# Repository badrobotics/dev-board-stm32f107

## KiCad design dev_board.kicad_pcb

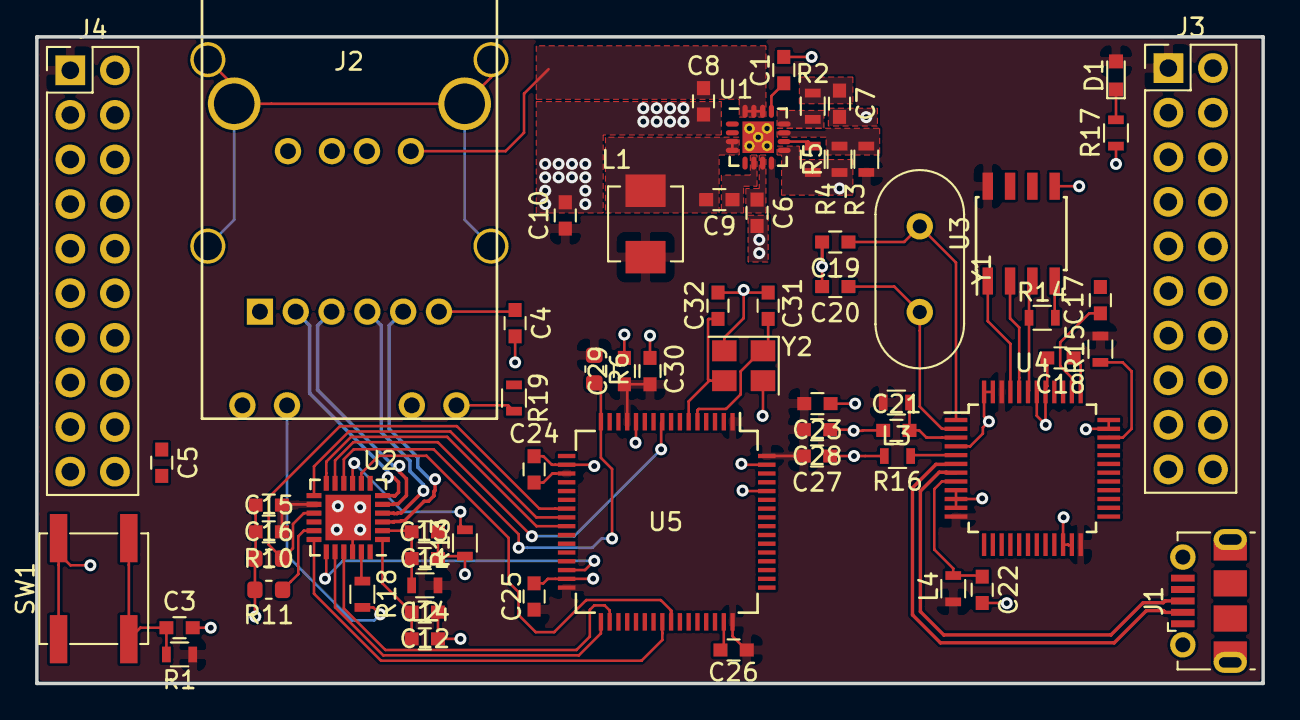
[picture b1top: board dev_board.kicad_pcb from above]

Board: 2 copper layers, 69.9 x 36.8 mm, 63 parts (0 on the bottom side), 59 nets.

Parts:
C1: 2200p; C_0603
C3, C17, C18, C19, C20, C21, C22, C31, C32: C_Small; C_0603
C4, C5: 0.1uF; C_0603
C6: 2.2u; C_0603
C7: 330p; C_0603
C8, C11, C12, C15: 22u; C_0603
C9, C13, C14, C16: 0.1u; C_0603
C10: 47u; C_0603
C23, C24, C25, C26, C27: 100nF; C_0603
C28: 4.7uF; C_0603
C29: 10nF; C_0603
C30: 1uF; C_0603
D1: LED; LED_0603
J1: USB_B_Micro; USB_Micro-B_Molex-105017-0001
J2: ARJ-169
J3, J4: Conn_02x10_Odd_Even; Pin_Header_Straight_2x10_Pitch2.54mm
L1: 0.47u; L_Vishay_IHLP-1616
L2: Ferrite_Bead; L_0603
L3, L4: Ferrite_Bead_Small; L_0603
R1: 10k; R_0603
R2: 20k; R_0603
R3: 210k; R_0603
R4: 115k; R_0603
R5: 25.5; R_0603
R6, R10: 1K; R_0603_1608Metric
R11: 10K; R_0603_1608Metric
R13: 6.49K 1%; R_0603
R14, R15, R16: R_Small; R_0603
R17, R18, R19: R; R_0603
SW1: SW_Push; SW_SPST_EVPBF
U1: LTC3604_UD; QFN-16-1EP_3x3mm_Pitch0.5mm_ThermalVias
U2: KSZ8081RND; QFN-24-1EP_4x4mm_Pitch0.5mm
U3: 93LCxxB; SOIC-8_3.9x4.9mm_Pitch1.27mm
U4: FT232H; LQFP-48_7x7mm_Pitch0.5mm
U5: STM32F107RCTx; LQFP-64_10x10mm_Pitch0.5mm
Y1: Crystal; Crystal_HC49-U_Vertical
Y2: Crystal_GND24; Crystal_SMD_3225-4pin_3.2x2.5mm

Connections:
+1V8: C17.1, U4.38
+3V3: C10.1, C15.1, C16.1, C23.2, C24.2, C25.2, C26.2, C27.2, C28.2, C29.1, C30.1, D1.2, J3.1, J4.1, L1.2, L2.2, L3.2, L4.2, R1.1, R4.1, R6.1, R15.2, U1.8, U2.14, U3.8, U4.12, U4.24, U4.39, U4.40, U4.46, U5.1, U5.13, U5.19, U5.32, U5.48, U5.64
+5V: C8.1, J2.U1, J3.2, J4.2, U1.14, U1.15, U1.16
/NRST: C3.1, R1.2, SW1.2, U2.24, U5.7
/RX_N: J2.P5, U2.3
/RX_P: J2.P4, U2.4
/TCK: U4.13, U5.49
/TDI: U4.14, U5.50
/TDO: U4.15, U5.55
/TMS: U4.16, U5.46
/TX_N: J2.P3, U2.5
/TX_P: J2.P2, U2.6
/USB_PROG_D+: J1.3, U4.7
/USB_PROG_D-: J1.2, U4.6
/ethernet_phy_ksz8081/1.2V_INTERNALLY_REGULATED: C12.1, C14.1, U2.1
/ethernet_phy_ksz8081/3.3V_QUIET: C11.1, C13.1, L2.1, U2.2
/ethernet_phy_ksz8081/INTRP: U2.18, U5.40
/ethernet_phy_ksz8081/LED0: R18.2, U2.23
/ethernet_phy_ksz8081/PHY_REF_RES: R13.1, U2.9
/ethernet_phy_ksz8081/RMII_RXER: R11.1, U2.17
/power_supply/BST: C9.1, U1.6
/power_supply/FB: R4.2, R5.1, U1.11
/power_supply/INTVcc: C6.1, U1.7
/power_supply/ITH: R2.1, U1.12
/power_supply/RT: R3.1, U1.10
/power_supply/SW: C9.2, L1.1, U1.3, U1.4
/stm32f107/ETH_RMII_CRS_DV: R10.1, U2.15, U5.23
/stm32f107/ETH_RMII_MDC: U2.11, U5.9
/stm32f107/ETH_RMII_MDIO: R6.2, U2.10, U5.16
/stm32f107/ETH_RMII_RXD0: U2.13, U5.24
/stm32f107/ETH_RMII_RXD1: U2.12, U5.25
/stm32f107/ETH_RMII_TXD0: U2.20, U5.33
/stm32f107/ETH_RMII_TXD1: U2.21, U5.34
/stm32f107/ETH_RMII_TX_EN: U2.19, U5.30
/stm32f107/MCO: U2.8, U5.41
/stm32f107/OSC1: C31.1, U5.5, Y2.1
/stm32f107/OSC2: C32.2, U5.6, Y2.3
/stm32f107/OTG_FS_N: J2.U2, U5.44
/stm32f107/OTG_FS_P: J2.U3, U5.45
GND: C1.2, C3.2, C4.2, C5.2, C6.2, C7.2, C8.2, C10.2, C11.2, C12.2, C13.2, C14.2, C15.2, C16.2, C17.2, C18.2, C19.2, C20.2, C21.1, C22.2, C23.1, C24.1, C25.1, C26.1, C27.1, C28.1, C29.2, C30.2, C31.2, C32.1, J1.5, J1.6, J2.13, J2.15, J2.U4, J3.3, J3.4, J4.3, J4.4, R3.2, R5.2, R10.2, R11.2, R13.2, R16.2, R17.1, SW1.1, U1.9, U1.17, U2.22, U2.25, U3.5, U4.4, U4.9, U4.10, U4.11, U4.22, U4.23, U4.35, U4.36, U4.41, U4.42, U4.47, U4.48, U5.12, U5.18, U5.31, U5.47, U5.60, U5.63, Y2.2, Y2.4
unnamed: C1.1, U1.13
unnamed: C4.1, J2.P6
unnamed: C5.1, J2.P1
unnamed: C7.1, R2.2
unnamed: C18.1, U4.37
unnamed: C19.1, U4.1, Y1.1
unnamed: C20.1, U4.2, Y1.2
unnamed: C21.2, L3.1, U4.3
unnamed: C22.1, L4.1, U4.8
unnamed: D1.1, R17.2
unnamed: J2.14, R18.1
unnamed: J2.16, R19.1
unnamed: J2.SH1, J2.SH2, J2.SH4, J2.SH5
unnamed: R14.1, U3.3, U4.43
unnamed: R14.2, U3.4
unnamed: R15.1, U4.34
unnamed: R16.1, U4.5
unnamed: U3.1, U4.45
unnamed: U3.2, U4.44

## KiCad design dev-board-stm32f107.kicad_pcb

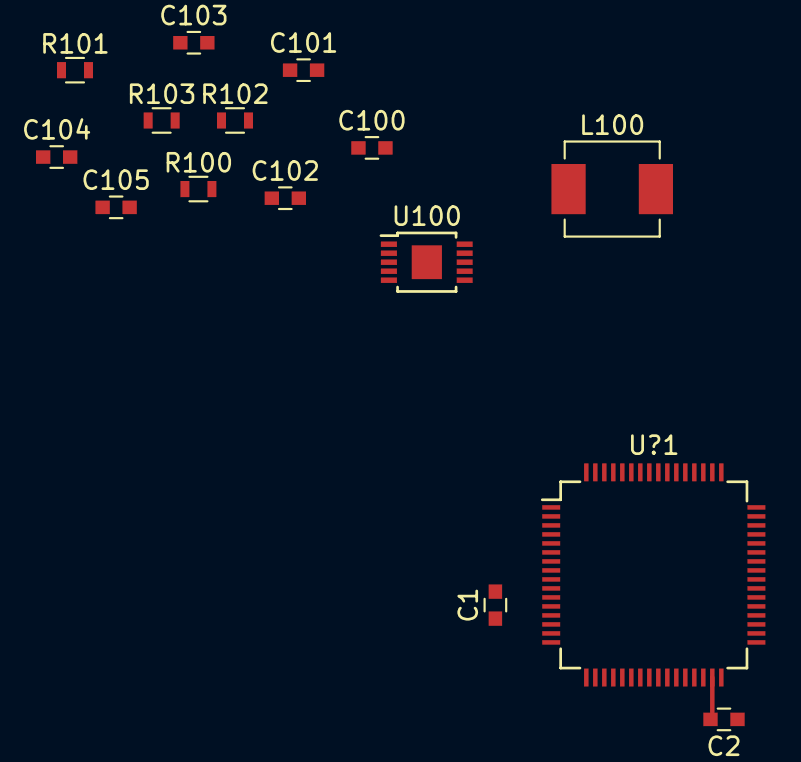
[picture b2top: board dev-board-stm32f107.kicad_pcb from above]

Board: 2 copper layers, 15 parts (0 on the bottom side), 10 nets.

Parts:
C1, C2: C; C_0603
C100: 4.7uF; C_0603
C101: 1uF; C_0603
C102: 10nF; C_0603
C103: 0.1uF; C_0603
C104: 10pF; C_0603
C105: 22uF; C_0603
L100: 2.2uH; L_Vishay_IHLP-2020
R100: 18.2k; R_0603
R101: 100k; R_0603
R102: 309k; R_0603
R103: 1M; R_0603
U100: LT8609; MSOP-10-1EP_3x3mm_Pitch0.5mm
U?1: STM32F107xx; LQFP-64_10x10mm_Pitch0.5mm

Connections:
+3V3: C1.1, C2.1, C104.1, C105.1, L100.2, R101.1, R103.1, U?1.1, U?1.13, U?1.19, U?1.32, U?1.48, U?1.64
/power_supply/P_GOOD: R101.2, U100.8
/power_supply/Vin: C100.1, U100.9, U100.10
GND: C1.2, C2.2, C100.2, C101.2, C102.2, C105.2, R100.2, R102.2, U100.11, U?1.12, U?1.18, U?1.31, U?1.47, U?1.63
unnamed: C101.1, U100.3
unnamed: C102.1, U100.7
unnamed: C103.1, L100.1, U100.2
unnamed: C103.2, U100.1
unnamed: C104.2, R102.1, R103.2, U100.6
unnamed: R100.1, U100.4

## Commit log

2018-06-22 Add README.md
2018-06-23 added kicad project files. Don't know a ton about what a good directory structure is for kicad yet, so it's just the files. Will also need to clone the symbol library repo.
2018-06-27 added a power supply circuit ripped right from the 8609 datasheet. probably fine for 5V to 3.3V
2018-06-27 added footprints for power components. Updated netlist.
2018-08-21 All of the phy stuff I did before I ragequit
2018-08-29 More phy progress
2018-09-29 Finished PHY circuit.
2018-09-29 added ft232h circuit for usb to jtag conversion.
2018-09-29 added mcu support circuitry and template.
2018-09-29 Updating project to kicad 5. Added USB ports.
2019-01-27 a bunch of stuff I guess. mostly layout.
2019-01-27 more layout
2019-02-02 layout
2019-02-03 updated power supply circuit. Better bandwidth, added softstart cap
2019-02-09 some layout changes? picked some random oscillator packages.
2019-02-16 pcb updates or something
2019-02-21 redirected 3D models for custom footprints on PCB
2019-03-10 revised ethernet layout
